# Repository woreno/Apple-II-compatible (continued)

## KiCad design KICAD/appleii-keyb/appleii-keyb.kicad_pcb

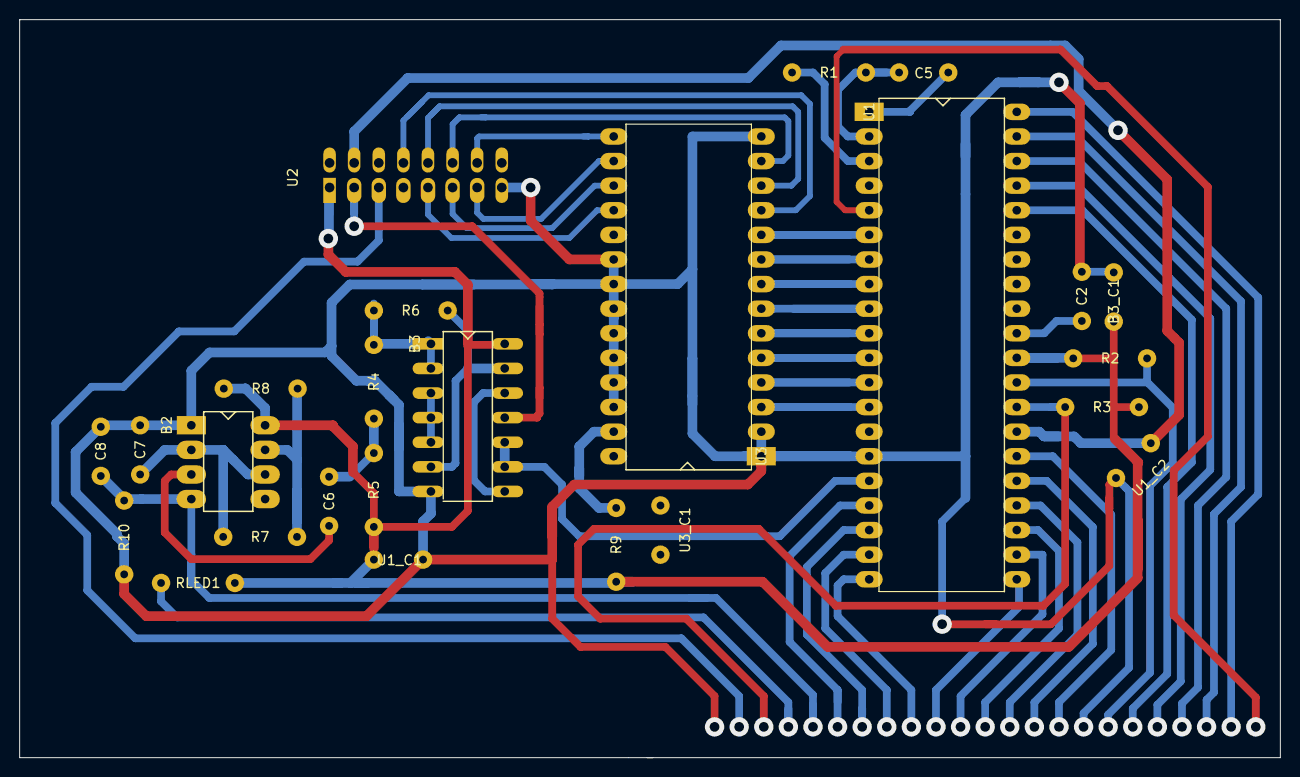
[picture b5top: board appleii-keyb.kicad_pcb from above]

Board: 2 copper layers, 130.2 x 76.2 mm, 25 parts (0 on the bottom side), 36 nets.

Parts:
B2: 555; standard_DIP_8pins
B3: 74LS00; standard_DIP_14OvalPins
B3_C1: 0.1u; standard_2pins_half
C2: 22nF; standard_2pins_half
C5: 47pF; standard_2pins_half
C6, C7, C8: 0.1u; standard_2pins_half
R1: 51K; standard_2pins
R2, R3, R5, R6, R9: 4.7K; standard_2pins
R4: 220; standard_2pins
R7: 220K; standard_2pins
R8: 510K; standard_2pins
R10: 3K; standard_2pins
RLED1: 250; standard_2pins
U1: AY-5-3600-PRO; standard_DIP_40pins_doubleBody
U1_C1, U1_C2, U3_C1: 0.1u; standard_2pins_half
U2: APPLEII_KEYBCON; Conector2x8_Oval
U3: PPROM_28C65_256; standard_DIP_28pins_doubleBody

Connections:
/5V: B2.8, B3.14, B3_C1.1, R2.1, R3.1, R5.2, R8.1, R9.1, RLED1.1, U1.30, U1_C1.2, U2.1, U3.28, U3_C1.1
/-12V: U1.27, U1_C2.1, U2.15
/ASCII_0: U2.12, U3.12
/ASCII_1: U2.13, U3.11
/ASCII_2: U2.10, U3.15
/ASCII_3: U2.11, U3.13
/ASCII_4: U2.6, U3.17
/ASCII_5: U2.5, U3.18
/ASCII_6: U2.7, U3.16
/CTRL_KEY: R3.2, U1.28
/DATA_READY: B3.9, B3.10, U1.16
/GND: B2.1, B3.7, B3_C1.2, C2.2, C7.2, C8.2, R10.2, U1.15, U1_C1.1, U1_C2.2, U2.8, U3.1, U3.2, U3.14, U3.20, U3.21, U3.22, U3.23, U3.24, U3.25, U3.26, U3_C1.2
/REP_KEY: B2.4, C8.1, R10.1
/SCAN_D0: U1.6, U3.10
/SCAN_D1: U1.7, U3.9
/SCAN_D2: U1.8, U3.8
/SCAN_D3: U1.9, U3.7
/SCAN_D4: U1.10, U3.6
/SCAN_D5: U1.11, U3.5
/SCAN_D6: U1.12, U3.4
/SCAN_D7: U1.13, U3.3
/SHIFT_KEY: R2.2, U1.29
/STROBE: B3.11, U2.2
unnamed: B2.2, B2.6, C7.1, R7.2
unnamed: B2.3, C6.1
unnamed: B2.7, R7.1, R8.2
unnamed: B3.1, B3.2, R4.1, R6.2
unnamed: B3.3, B3.4, B3.5
unnamed: B3.8, B3.12
unnamed: B3.6, B3.13, R6.1
unnamed: C2.1, U1.31
unnamed: C5.1, R1.1, U1.2
unnamed: C5.2, U1.1
unnamed: C6.2, R4.2, R5.1
unnamed: R1.2, U1.3
unnamed: R9.2, U3.27
